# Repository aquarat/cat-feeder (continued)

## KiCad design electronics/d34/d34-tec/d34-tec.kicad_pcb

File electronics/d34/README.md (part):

# D34 hand-soldered controller (three vertical cards)

**Status: generated, ERC/DRC-checked design files. Not fabricated, not
soldered, not powered, no firmware.**

- Rationale, power budget, TVS analysis and open questions: [kb/d34-controller.md](../../kb/d34-controller.md).
- Decision: [D34](../../kb/decisions.md).

Bare 2-layer boards (1.6 mm FR-4, 1 oz), fabrication only. Every part is
through-hole or a plug-in module. Two upload packages per card:
`<card>-pcbtrain.zip` (PCB Train / Newbury Electronics, UK; recommended UK
fab) and `<card>-jlcpcb-gerbers.zip` (JLCPCB, much cheaper). Components:
RS Components UK except one Farnell line and two module retailers; the
sourced BOM, totals and fab comparison are in
[kb/d34-sourcing.md](../../kb/d34-sourcing.md).
3D envelopes for CAD: [`parts3d.json`](parts3d.json) (schema below).

All three cards are **81 × 47 mm**, sized to the CAD-checked bay (44 radial ×
85 tangential × 51 mm high). Each stands in a floor slot with its plane
tangential and components facing the axis. The top long edge takes a
printed clip. 3 mm long-edge bands are free of pads and courtyards.

| Card | Bay | Contents |
|---|---|---|
| [`d34-ctrl`](d34-ctrl/) | 45° | Socketed ESP32-DevKitC-32E, lid/leak/home/UI/DPS-UART headers, TEC watchdog (74HC123) and defrost latch (74HC573). Only 5 V and 3.3 V. |
| [`d34-pwr`](d34-pwr/) | 225° | 24 V brick entry, reverse FET, TVS, 7.5 A DPS fuse, 1.1 A PTC aux, TRACO 12 V 2 A / 5 V 1 A bucks, DPS5005 feed, StepStick (VMOT 12 V) + motor, one 1-Wire header per bus. |
| [`d34-tec`](d34-tec/) | 315° | K1 cut-off and K2 reversal relays (2N3904 low sides, K2 hold-up), thermostat loop, DPS output in, TEC out, three fan headers with IRLZ44N low sides and a 0.5 A polyfuse each. |

## Inter-card leads (keyed, same pin order both ends; checked by `test_d34.py`)

| Lead | Type | Pins |
|---|---|---|
| ctrl J1 ↔ pwr J9 | JST XH-11 | 1-2 +5 V, 3-4 GND, 5 +3V3, 6 STEP, 7 DIR, 8 EN, 9 TMC UART, 10 1-Wire A, 11 1-Wire B |
| ctrl J2 ↔ tec J9 | JST XH-12 | 1-2 GND, 3 K1_ON, 4 K2_ON, 5 THERMO_OK, 6 GND, 7-9 FAN1-3 PWM, 10-11 TACH1-2, 12 GND |
| pwr J3 → tec J1 | JST VH-3 | 1 +12 V, 2 GND, 3 +12 V |

## Card connectors

Pin 1 is the square pad or the silkscreen triangle.

| Card | Ref | Type | Pins |
|---|---|---|---|
| pwr | J1 | Mini-Fit Jr 2 | 1 +24 V in, 2 GND (brick) |
| pwr | J2 | Phoenix MSTB 2 | DPS5005 input: 1 IN+ (7.5 A fused), 2 IN− |
| pwr | J8 | JST VH-4 | Motor 2B 2A 1A 1B (17HS08-1004S: confirm coil pairs with a meter) |
| pwr | J4 / J6 | XH-3 | 1-Wire bus A (chamber air + food probes) / bus B (hot sink + room): GND, DQ, 3V3. The harness Y-splices each bus to its probes; more probes can join either bus. |
| tec | J2 | Mini-Fit Jr 6 | DPS5005 output: 1-3 OUT+, 4-6 OUT− (OUT− is **not** ground). The lead populates only pins 1 and 4 (one 18 AWG wire per pole, ≤ 5 A on a 9 A contact); the 6-way housing keeps it unpluggable into the 4-way TEC header. |
| tec | J3 | Mini-Fit Jr 4 | TEC 2S2P: 1 A, 2 B, 3 A, 4 B (one string per pair) |
| tec | J4 | JST VH-2 | Thermostat loop: 1 +12 V out, 2 return to K1 coil. Four RS PRO T24A060ASF2-15 NC (open 60 °C) in series. |
| tec | J5 | 4-pin fan | FAN1 (NF-A12x25): GND, +12 V via 0.5 A PTC, TACH, PWM (NPN open collector, **inverted**) |
| tec | J6 | 4-pin fan | FAN2 (blower): switched low side (IRLZ44N), +12 V via 0.5 A PTC, TACH, NC |
| tec | J7 | 4-pin fan | FAN3 spare: switched low side (IRLZ44N), +12 V via 0.5 A PTC, NC, NC (fan or external 12 V relay ≤ 0.4 A) |
| ctrl | J3 | XH-3 | Home sensor (DRV5023 hall, 3.3 V, open drain into the 10 k pull-up): GND, SIG, 3V3 |
| ctrl | J4 | XH-4 | SENSE: 1 GND, 2 LID (reed to GND, 10 k pull-up), 3 LEAK (basin-full pins, 47 k pull-up, 10 k series to ADC), 4 GND. Two cables, one housing. |
| ctrl | J6 | XH-5 | Panel: GND, 3V3, LED (330 Ω fitted), BUTTON (to GND), GND |
| ctrl | J11 | XH-4 | DPS5005 UART 3.3 V: GND, DPS-TX, DPS-RX, NC. DPS end: the 4-pin 1.25 mm (JST-GH type) comms socket; make the lead from the cable supplied with the DPS comms kit, meter GND and the idle-high TX first (see kb/d34-sourcing.md). |

**StepStick (pwr U4).** BIGTREETECH TMC2209 V1.3 is the intended driver
(pinout from BTT's V1.3 schematic, `datasheets/btt_tmc2209_v13_sch.pdf`).
- **VMOT is +12 V** from the TSR 2-24120N, not the 24 V brick, so the TVS
  clamp (30–33 V) can never reach the TMC2209 (32 V abs max).
- Pin 4 (PDN_UART) is wired to the ESP32 single-wire UART: TX via 1 k (ctrl
  R6), RX direct. BTT V1.3 has no series resistor on the module, so R6 is needed.
- Pins 5 and 6 are linked to each other only. BTT V1.3: pin 5 is not connected
  on the module, pin 6 is CLK with a 20 k pull-down (internal clock). A4988:
  RESET tied to SLEEP, which the Pololu carrier pulls up (Pololu's own advice).
- MS1/MS2 are open: the TMC2209's internal pull-downs give UART address 0.
- A Pololu A4988 also fits, but only at full step. Firmware must then hold
  IO17 low and keep IO16 as an input, so that MS3 = 0.

## ESP32 GPIO map

| GPIO | Use | GPIO | Use |
|---|---|---|---|
| IO0 | Button (also BOOT) | IO19 | EN (active low) |
| IO2 | Status LED (panel + on-board) | IO21 / IO22 | DPS RX / TX |
| IO4 / IO13 | 1-Wire A / B | IO23 | HOME |
| IO5 | FAN3 on/off | IO25 | DEFROST_REQ |
| IO12 | FAN1 PWM (10 k strap pull-down) | IO26 | DEFROST_FB |
| IO14 | FAN2 on/off (switched DC) | IO27 | LID |
| IO15 | DIR | IO32 | TEC_EN |
| IO16 / IO17 | TMC UART RX / TX | IO33 | WDT_KICK |
| IO18 | STEP | IO34 / IO35 | TACH1 / TACH2 |
| IO36 | THERMO_OK | IO39 | LEAK (ADC) |

## TEC firmware contract (hardware-enforced parts and firmware rules)

Revised 2026-10-26 after the simulation round ([kb/d34-simulation.md](../../kb/d34-simulation.md)).

1. **K1 closes only while all of these hold:**
   - TEC_EN (IO32) is high;
   - IO33 (WDT_KICK) shows rising edges at **≥ 10 Hz** (74HC123 timeout 470 k × 1 µF ≈ 0.47 s nominal,
     **0.32–0.65 s** over K = 0.69–1.36 at 3.3 V, C ±10 %, R ±1 %);
   - +12 V is present and every thermostat is closed (the K1 coil is fed through them).

   Reset, a crash, a stuck pin, an unplugged lead or a lost 12 V rail opens K1.
2. **Firmware rules the hardware cannot enforce:**
   - toggle WDT_KICK from the control loop in software, **never from a hardware PWM/LEDC/timer**
     (a hung CPU with a running PWM would keep K1 closed);
   - **never pulse TEC_EN as a keep-alive**: a TEC_EN rising edge while WDT_KICK is high retriggers the
     74HC123 through its CLR input;
   - read the blower tach (TACH2) only while FAN2 is fully on: FAN2/FAN3 are now **switched DC**
     (no 25 kHz PWM), and the tach is referenced to the switched ground. FAN1 keeps 25 kHz PWM (inverted).
3. **K2 (defrost polarity)** follows DEFROST_REQ only while the latch is transparent: K1 commanded off for
   longer than the 74HC123 half-2 delay (0.32–0.65 s). LE edges are now CMOS-fast. K2 also has a
   hold-up (C1 220 µF): after its drive drops it stays energised for up to ~0.25 s, so on any supply loss
   K1 (fast diode + 15 V zener release) always opens first. Defrost entry and exit:
   - DPS output off (Modbus);
   - TEC_EN low;
   - wait **≥ 0.8 s** (latch delay max 0.65 s);
   - set or clear DEFROST_REQ;
   - wait **≥ 400 ms** (K2 transfer; on exit K2 is held up to ~0.25 s by C1), then check DEFROST_FB;
   - re-arm (TEC_EN high + kicks), wait ≥ 50 ms for K1 to close;
   - only then DPS output on. **Keep the DPS output off until K1 is re-armed.**
4. **After any reset or brown-out** run the full contract from boot before re-arming K1: the 74HC573
   contents (K2 command) are undefined at power-up. Keep TEC_EN low and the DPS output off, drive
   DEFROST_REQ to the wanted state, wait ≥ 0.8 s (latch delay ≤ 0.65 s, so the latch has loaded it), wait
   ≥ 0.4 s, check DEFROST_FB, then re-arm and only then turn the DPS output on. Timings as in
   `sim/firmware_contract.json` (owned by the simulation agent).
5. **12 V undervoltage cut-off (hardware, tec card):** the thermostat loop that feeds K1's coil is switched
   by Q6 (BC327) under a TL431 comparator: K1 drops below ~9.4 V on +12 V and can re-close only above
   ~10.3 V. While it is tripped THERMO_OK reads low, the same as an open thermostat.
6. **THERMO_OK** (IO36) reads about 3.0 V (2.85–3.15 V) when the thermostat loop is closed; reading it with
   the ADC (threshold ~1.4 V) gives more margin than a digital read. IO36 is now fed through 47 k with a
   BAT42 clamp to GND (a thermostat opening drags the loop to about −15 V for a few ms).
7. **Reversed-brick ring snubber:** 2.2 Ω + 1 µF in series across the inlet socket's +24 V and 0 V pins
   (off-board, at the Kycon socket), keeping the reversed-plug ring at J1 within Q1's 55 V rating.

## Files (per card directory)

| File | Purpose |
|---|---|
| `<card>.kicad_pro/.kicad_sch/.kicad_pcb` | KiCad 9 project; local libs `d34.kicad_sym`, `../d34.pretty` |
| `<card>.kicad_dru` | Copy of [`../dfm/jlcpcb-2layer-recommended.kicad_dru`](../dfm/README.md) |
| `<card>-pcbtrain.zip`, `pcbtrain/` | Upload to PCB Train: RS-274X without X2, Excellon PTH/NPTH, README.txt |
| `<card>-jlcpcb-gerbers.zip`, `gerbers/` | Upload to JLCPCB (Gerber X2 + Excellon PTH/NPTH) |
| `<card>-bom.csv` | Card BOM with supplier, stock number, pack, datasheet and verification state; off-board mating parts |
| `erc.*`, `drc.*`, `validation.json` | Check results for exactly these files |
| `envelope.json` | Courtyards and body/mated heights for CAD |
| `views/` | `render-top/bottom.png`, `top/bottom/assembly.svg`, `schematic.pdf`, `board-only.step` |

Shared sources:
- `design.py`: connectivity, placement and hand-placed high-current copper.
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
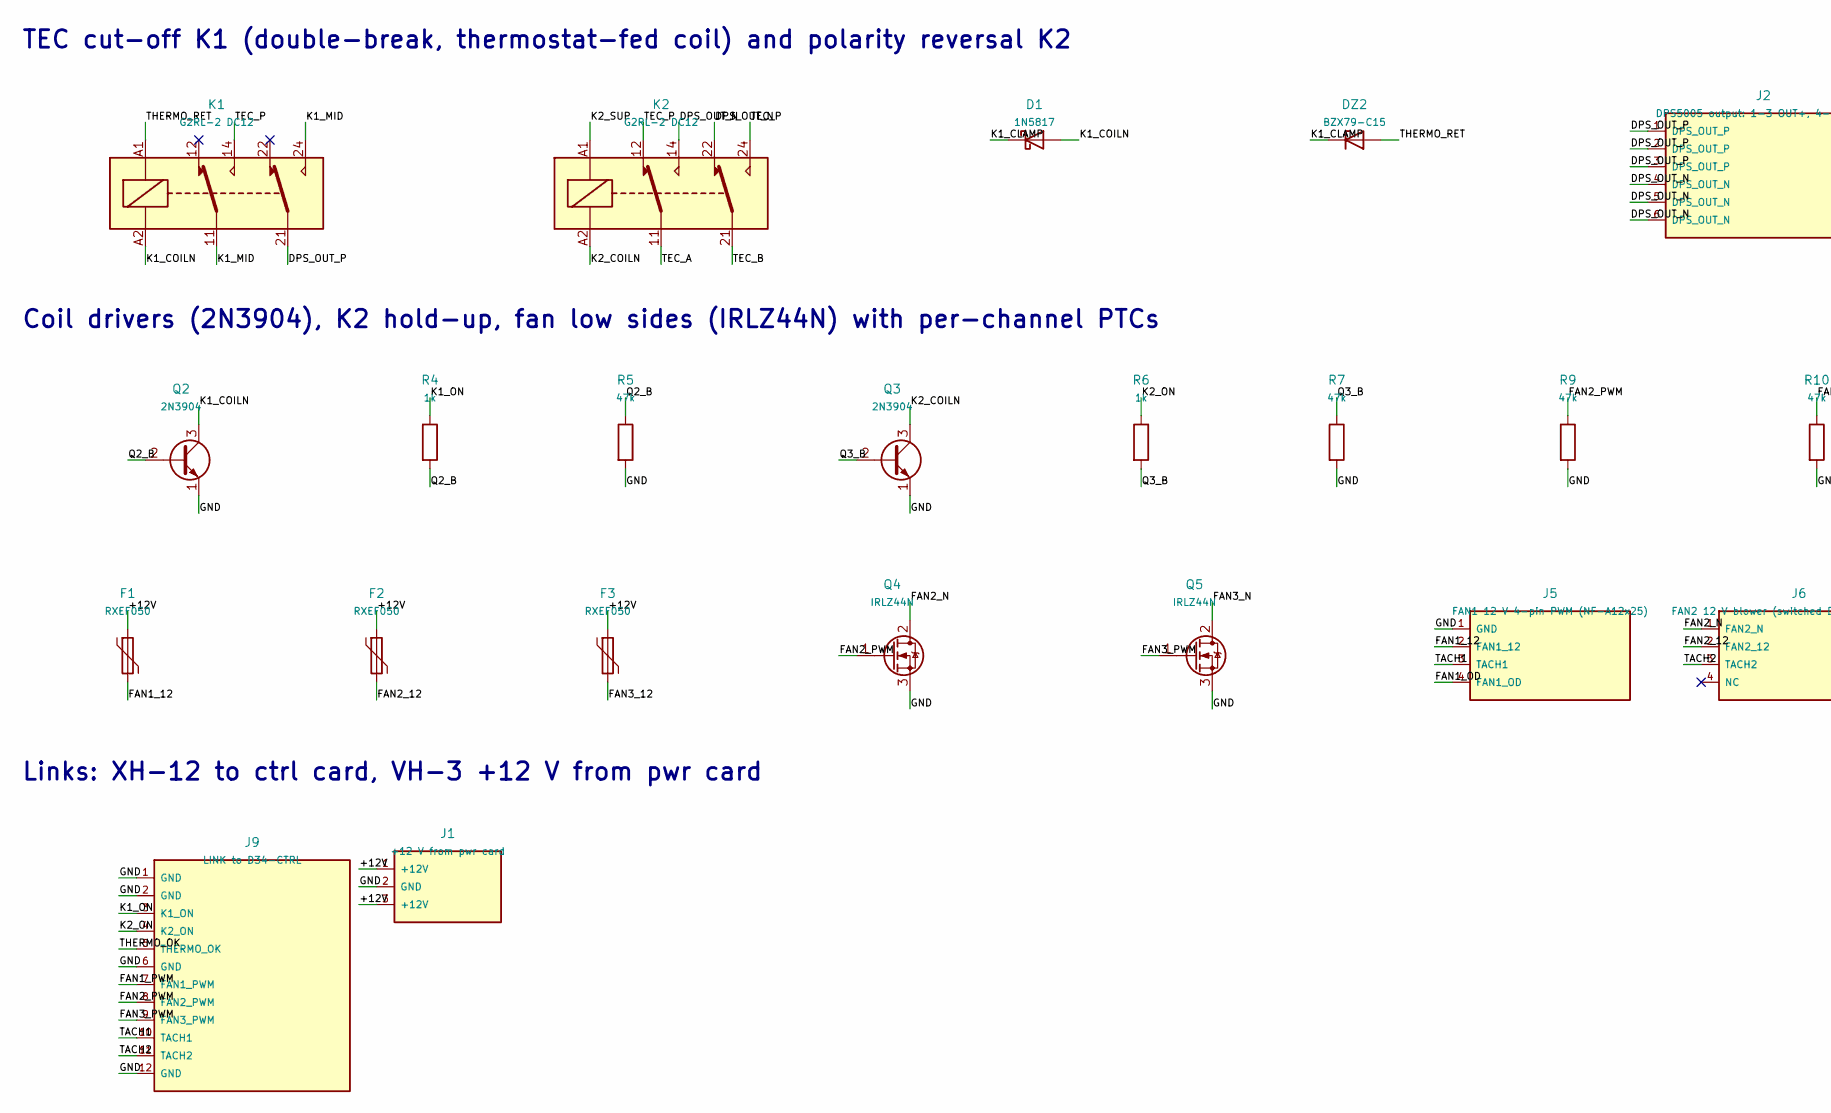
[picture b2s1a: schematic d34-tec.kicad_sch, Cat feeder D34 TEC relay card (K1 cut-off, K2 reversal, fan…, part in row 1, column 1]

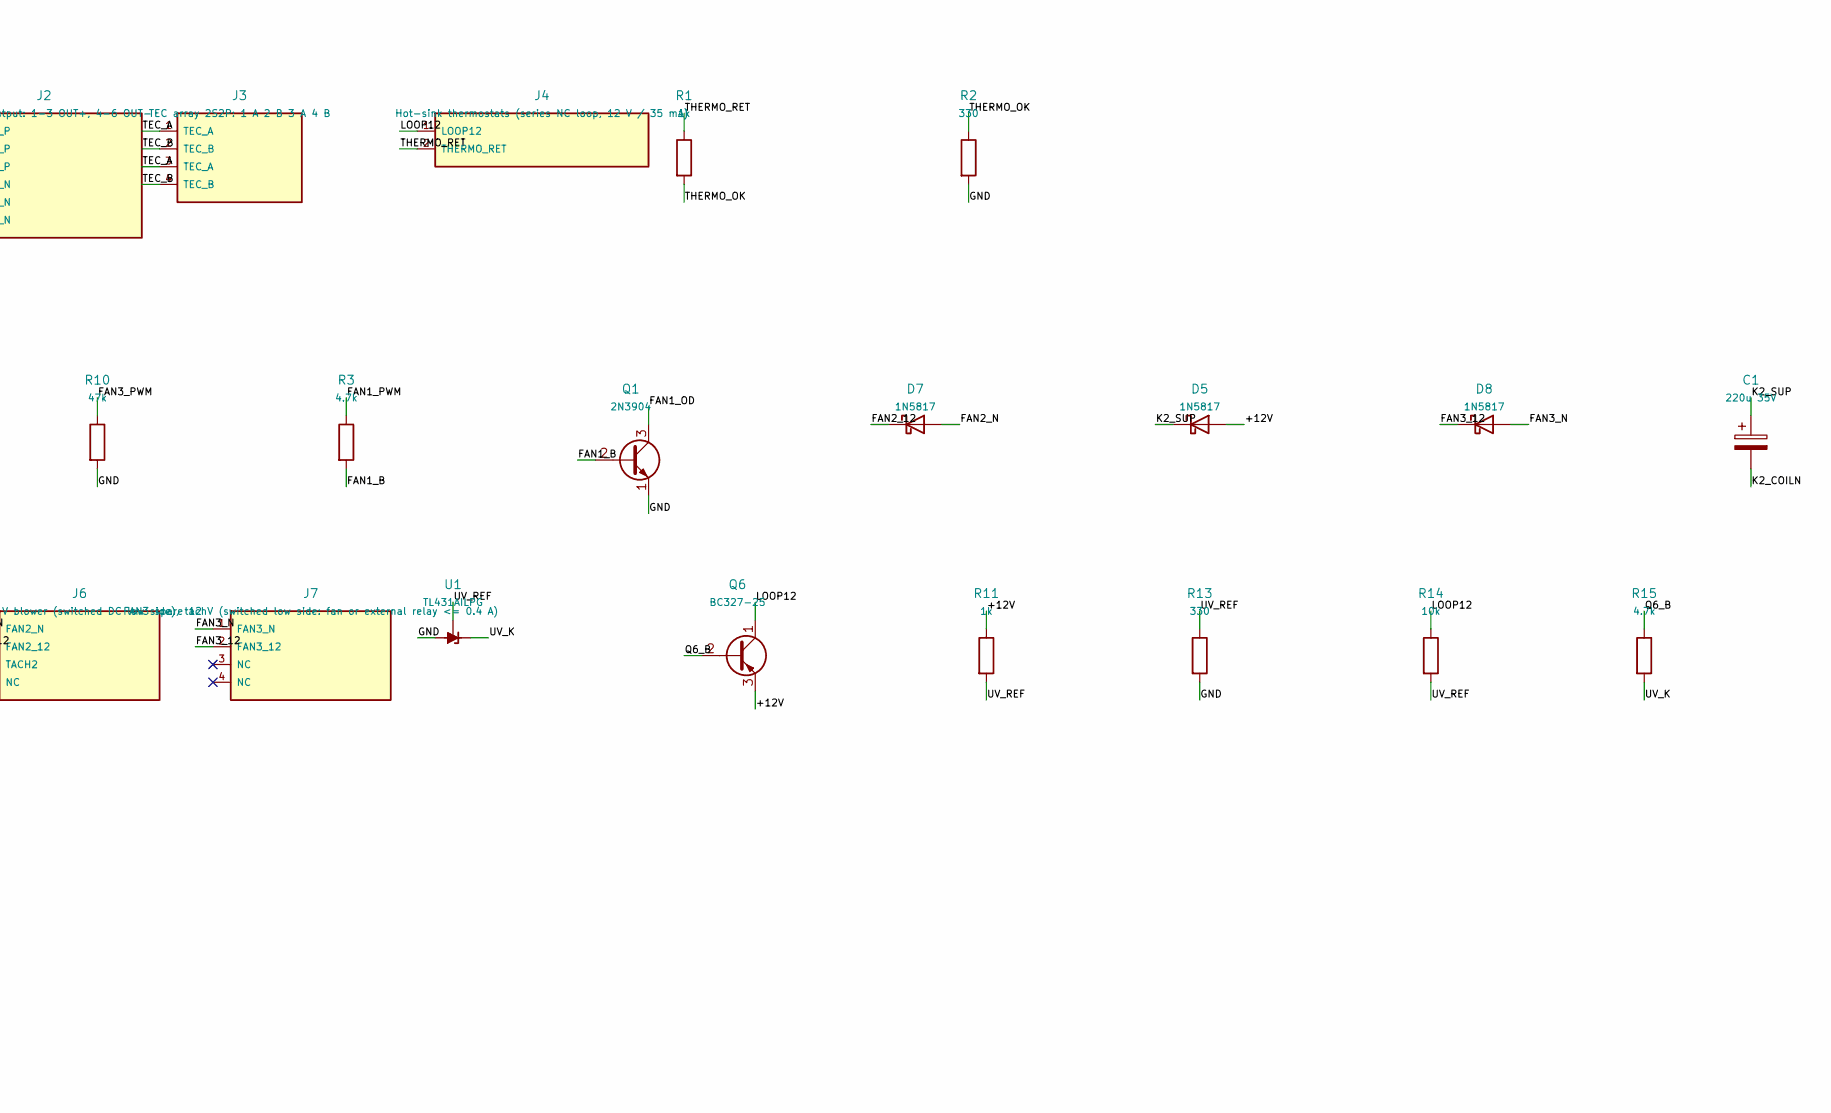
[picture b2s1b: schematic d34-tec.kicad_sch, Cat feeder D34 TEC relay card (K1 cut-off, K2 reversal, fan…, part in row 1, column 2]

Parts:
C1: 220u 35V; CP_Radial_D8.0mm_P3.50mm; MPN EEU-FR1V221
D1, D5, D7, D8: 1N5817; D_DO-41_SOD81_P2.54mm_Vertical_AnodeUp; MPN 1N5817RLG
DZ2: BZX79-C15; D_DO-35_SOD27_P2.54mm_Vertical_AnodeUp; MPN BZX79-C15,133
F1, F2, F3: RXEF050; PTC_Radial_L8.0mm_W3.2mm_P5.08mm; MPN RXEF050
J1: +12 V from pwr card; JST_VH_B3P-VH_1x03_P3.96mm_Vertical; MPN B3P-VH(LF)(SN)
J2: DPS5005 output: 1-3 OUT+, 4-6 OUT-; Molex_Mini-Fit_Jr_5566-06A_2x03_P4.20mm_Vertical; MPN 39-28-1063 (5566-06A)
J3: TEC array 2S2P: 1 A 2 B 3 A 4 B; Molex_Mini-Fit_Jr_5566-04A_2x02_P4.20mm_Vertical; MPN 39-28-1043 (5566-04A)
J4: Hot-sink thermostats (series NC loop, 12 V / 35 m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; JST_VH_B2P-VH_1x02_P3.96mm_Vertical; MPN B2P-VH(LF)(SN)
J5: FAN1 12 V 4-pin PWM (NF-A12x25); FanPinHeader_1x04_P2.54mm_Vertical; MPN 47053-1000
J6: FAN2 12 V blower (switched DC low side), tach; FanPinHeader_1x04_P2.54mm_Vertical; MPN 47053-1000
J7: FAN3 spare 12 V (switched low side: fan or extern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; FanPinHeader_1x04_P2.54mm_Vertical; MPN 47053-1000
J9: LINK to D34-CTRL; JST_XH_B12B-XH-A_1x12_P2.50mm_Vertical; MPN B12B-XH-A(LF)(SN)
K1, K2: G2RL-2 DC12; Relay_DPDT_Omron_G2RL-2; MPN G2RL-2 DC12
Q1, Q2, Q3: 2N3904; TO-92_Inline_Wide; MPN 2N3904BU
Q4, Q5: IRLZ44N; TO-220-3_Vertical; MPN IRLZ44NPBF
Q6: BC327-25; TO-92_Inline_Wide; MPN BC32725BU
R1, R4, R6, R11: 1k; R_Axial_DIN0204_L3.6mm_D1.6mm_P2.54mm_Vertical; MPN MF0204FTE52-1K
R2, R13: 330; R_Axial_DIN0204_L3.6mm_D1.6mm_P2.54mm_Vertical; MPN MF0204FTE52-330R
R3, R15: 4.7k; R_Axial_DIN0204_L3.6mm_D1.6mm_P2.54mm_Vertical; MPN MF0204FTE52-4K7
R5, R7, R9, R10: 47k; R_Axial_DIN0204_L3.6mm_D1.6mm_P2.54mm_Vertical; MPN MF0204FTE52-47K
R14: 10k; R_Axial_DIN0204_L3.6mm_D1.6mm_P2.54mm_Vertical; MPN MF0204FTE52-10K
U1: TL431AILPG; TO-92_Inline_Wide; MPN TL431AILPG

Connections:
/+12V: D5.2 (A), F1.1, F2.1, F3.1, J1.1 (+12V), J1.3 (+12V), Q6.3 (E), R11.1
/DPS_OUT_N: J2.4 (DPS_OUT_N), J2.5 (DPS_OUT_N), J2.6 (DPS_OUT_N), K2.14, K2.22
/DPS_OUT_P: J2.1 (DPS_OUT_P), J2.2 (DPS_OUT_P), J2.3 (DPS_OUT_P), K1.21
/FAN1_12: F1.2, J5.2 (FAN1_12)
/FAN1_B: Q1.2 (B), R3.2
/FAN1_OD: J5.4 (FAN1_OD), Q1.3 (C)
/FAN1_PWM: J9.7 (FAN1_PWM), R3.1
/FAN2_12: D7.1 (K), F2.2, J6.2 (FAN2_12)
/FAN2_N: D7.2 (A), J6.1 (FAN2_N), Q4.2 (D)
/FAN2_PWM: J9.8 (FAN2_PWM), Q4.1 (G), R9.1
/FAN3_12: D8.1 (K), F3.2, J7.2 (FAN3_12)
/FAN3_N: D8.2 (A), J7.1 (FAN3_N), Q5.2 (D)
/FAN3_PWM: J9.9 (FAN3_PWM), Q5.1 (G), R10.1
/GND: J1.2 (GND), J5.1 (GND), J9.1 (GND), J9.2 (GND), J9.6 (GND), J9.12 (GND), Q1.1 (E), Q2.1 (E), Q3.1 (E), Q4.3 (S), Q5.3 (S), R2.2, R5.2, R7.2, R9.2, R10.2, R13.2, U1.2 (A)
/K1_CLAMP: D1.1 (K), DZ2.1 (K)
/K1_COILN: D1.2 (A), K1.A2, Q2.3 (C)
/K1_MID: K1.11, K1.24
/K1_ON: J9.3 (K1_ON), R4.1
/K2_COILN: C1.2, K2.A2, Q3.3 (C)
/K2_ON: J9.4 (K2_ON), R6.1
/K2_SUP: C1.1, D5.1 (K), K2.A1
/LOOP12: J4.1 (LOOP12), Q6.1 (C), R14.1
/Q2_B: Q2.2 (B), R4.2, R5.1
/Q3_B: Q3.2 (B), R6.2, R7.1
/Q6_B: Q6.2 (B), R15.1
/TACH1: J5.3 (TACH1), J9.10 (TACH1)
/TACH2: J6.3 (TACH2), J9.11 (TACH2)
/TEC_A: J3.1 (TEC_A), J3.3 (TEC_A), K2.11
/TEC_B: J3.2 (TEC_B), J3.4 (TEC_B), K2.21
/TEC_P: K1.14, K2.12, K2.24
/THERMO_OK: J9.5 (THERMO_OK), R1.2, R2.1
/THERMO_RET: DZ2.2 (A), J4.2 (THERMO_RET), K1.A1, R1.1
/UV_K: R15.2, U1.3 (K)
/UV_REF: R11.2, R13.1, R14.2, U1.1 (REF)

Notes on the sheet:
TEC cut-off K1 (double-break, thermostat-fed coil) and polarity reversal K2
Coil drivers (2N3904), K2 hold-up, fan low sides (IRLZ44N) with per-channel PTCs
Links: XH-12 to ctrl card, VH-3 +12 V from pwr card

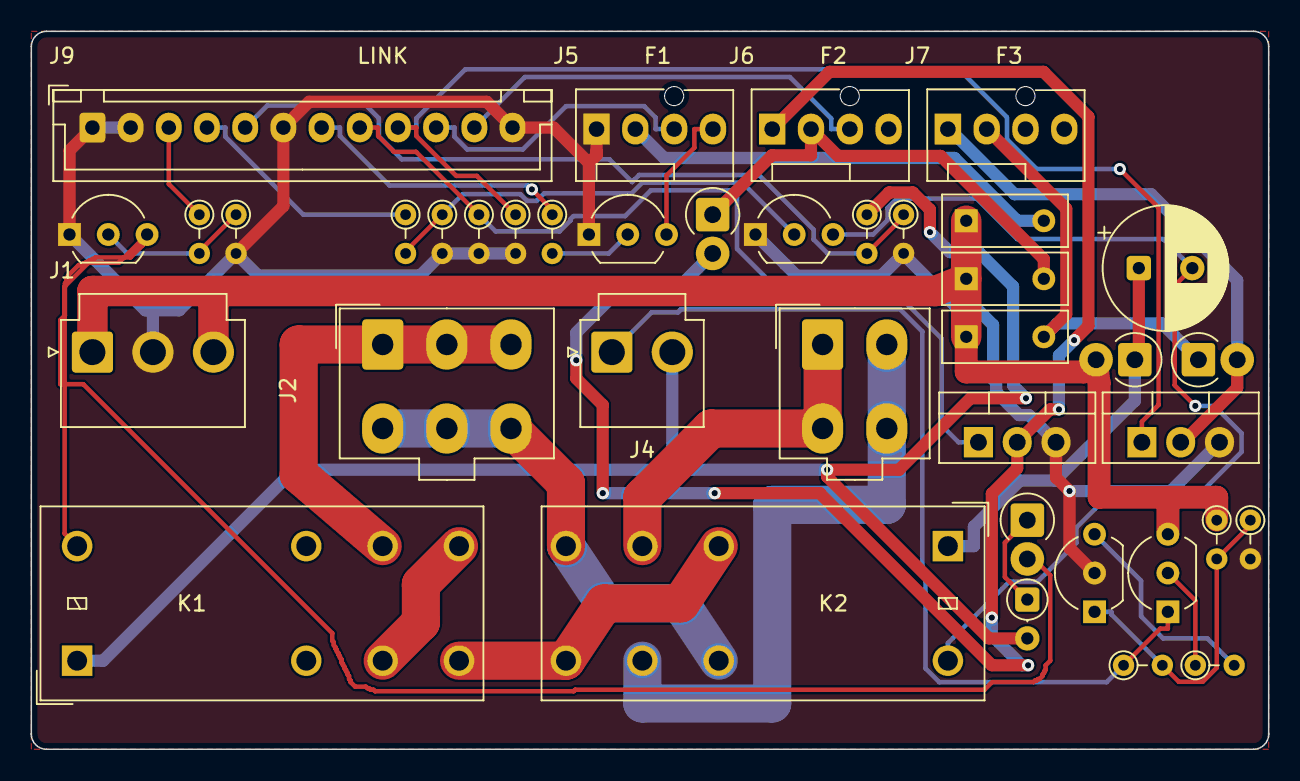
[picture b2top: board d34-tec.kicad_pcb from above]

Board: 2 copper layers, 81.0 x 47.0 mm, 39 parts (0 on the bottom side), 34 nets.

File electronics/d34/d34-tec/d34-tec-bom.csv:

Board,References,Qty,Value,Description,Manufacturer,MPN,KiCad footprint,Supplier,Stock no,Pack,Datasheet,Checked
d34-tec,K1 K2,2,,"DPDT relay 8 A, 12 V coil",Omron,G2RL-2 DC12,Relay_THT:Relay_DPDT_Omron_G2RL-2,RS,365-0585,1,omron_g2rl.pdf,"verified: 29 x 12.7 x 15.7 max, 1.3 mm holes on the KiCad grid, 33.3 mA / 360 ohm, 8 A 30 VDC (p2, p6); RS title says ""Aratas"" but listing is Omron, check marking on arrival"
d34-tec,D1 D7 D5 D8,4,,"Schottky 20 V 1 A, DO-41, mounted vertical",onsemi,1N5817RLG,Diode_THT:D_DO-41_SOD81_P2.54mm_Vertical_AnodeUp,RS,625-4972,5,1n5817-19.pdf,"verified: VF max 0.32 V @ 0.1 A, 0.45 V @ 1 A; 20 V; DO-41 (onsemi p2)"
d34-tec,DZ2,1,,"Zener 15 V 0.5 W, DO-35, mounted vertical (K1 fast-release clamp)",Nexperia,"BZX79-C15,133",Diode_THT:D_DO-35_SOD27_P2.54mm_Vertical_AnodeUp,RS,136-4852,100,bzx79.pdf,"verified: Vz 13.8-15.6 V @ 5 mA; SOD27 4.25 x 1.85 mm (p5, p9)"
d34-tec,J2,1,,6-pin Mini-Fit Jr vertical header,Molex,39-28-1063 (5566-06A),Connector_Molex:Molex_Mini-Fit_Jr_5566-06A_2x03_P4.20mm_Vertical,RS,484-1906,5,molex_5566_header.pdf,verified: SD-5566-002 (as 2-pin)
d34-tec,J3,1,,4-pin Mini-Fit Jr vertical header,Molex,39-28-1043 (5566-04A),Connector_Molex:Molex_Mini-Fit_Jr_5566-04A_2x02_P4.20mm_Vertical,RS,484-1899,5,molex_5566_header.pdf,verified: SD-5566-002 (as 2-pin)
d34-tec,J4,1,,2-pin JST VH header,JST,B2P-VH(LF)(SN),Connector_JST:JST_VH_B2P-VH_1x02_P3.96mm_Vertical,RS,820-1147,5,jst_vh.pdf,"verified: eVH pitch 3.96, hole 1.65-1.75, h 10.9, mated 16.5"
d34-tec,R1 R4 R6 R11,4,,"Resistor, metal film MF0204, 0.4 W, 1 %, axial, mounted vertical (2.54 mm)",Yageo,MF0204FTE52-1K,Resistor_THT:R_Axial_DIN0204_L3.6mm_D1.6mm_P2.54mm_Vertical,RS,199-7806,100,yageo_mf0.pdf,"verified: body 3.4+-0.3 x 1.9+-0.2 mm, lead 0.45 mm, M-forming P 6.0 mm (Yageo MF0 spec p3, p9)"
d34-tec,R2 R13,2,,"Resistor, metal film MF0204, 0.4 W, 1 %, axial, mounted vertical (2.54 mm)",Yageo,MF0204FTE52-330R,Resistor_THT:R_Axial_DIN0204_L3.6mm_D1.6mm_P2.54mm_Vertical,RS,199-7821,100,yageo_mf0.pdf,"verified: body 3.4+-0.3 x 1.9+-0.2 mm, lead 0.45 mm, M-forming P 6.0 mm (Yageo MF0 spec p3, p9)"
d34-tec,Q2 Q3 Q1,3,,"NPN 40 V 200 mA, TO-92",onsemi,2N3904BU,Package_TO_SOT_THT:TO-92_Inline_Wide,RS,843-1575,50,2n3904.pdf,"verified: E-B-C facing the flat, straight leads 1.15-1.39 mm, body 5.2 x 4.2 x 5.33 (p1, p7); h incl. ~2.5 mm standoff"
d34-tec,R5 R7 R9 R10,4,,"Resistor, metal film MF0204, 0.4 W, 1 %, axial, mounted vertical (2.54 mm)",Yageo,MF0204FTE52-47K,Resistor_THT:R_Axial_DIN0204_L3.6mm_D1.6mm_P2.54mm_Vertical,RS,199-7828,100,yageo_mf0.pdf,"verified: body 3.4+-0.3 x 1.9+-0.2 mm, lead 0.45 mm, M-forming P 6.0 mm (Yageo MF0 spec p3, p9)"
d34-tec,R3 R15,2,,"Resistor, metal film MF0204, 0.4 W, 1 %, axial, mounted vertical (2.54 mm)",Yageo,MF0204FTE52-4K7,Resistor_THT:R_Axial_DIN0204_L3.6mm_D1.6mm_P2.54mm_Vertical,RS,199-7830,100,yageo_mf0.pdf,"verified: body 3.4+-0.3 x 1.9+-0.2 mm, lead 0.45 mm, M-forming P 6.0 mm (Yageo MF0 spec p3, p9)"
d34-tec,C1,1,,"220 uF 35 V low-ESR electrolytic, 8 x 11.5 mm (K2 hold-up)",Panasonic,EEU-FR1V221,Capacitor_THT:CP_Radial_D8.0mm_P3.50mm,RS,766-0078,10,panasonic_fr.pdf,Panasonic FR (same 8 x 11.5 mm case/3.5 mm pitch as EEU-FR1H101 per FR p1/p6): 220 uF 35 V
d34-tec,F1 F2 F3,3,,Resettable PTC 0.5 A hold (per fan channel),Littelfuse,RXEF050,d34:PTC_Radial_L8.0mm_W3.2mm_P5.08mm,RS,517-6635,10,littelfuse_rxef.pdf,"verified: 0.50 A hold / 1.00 A trip, 72 V, 7.9 wide x 3.0 thick x 13.7 high max, spacing 4.3-5.8, lead 0.51 (RXEF p2, p4, p6)"
d34-tec,Q4 Q5,2,,"Logic-level N-MOSFET, TO-220 (fan low side; survives a PTC-limited short)",Infineon,IRLZ44NPBF,Package_TO_SOT_THT:TO-220-3_Vertical,Farnell,8651418,1,irlz44n.pdf,"Infineon datasheet saved: logic-level N-FET 55 V 47 A, VGS(th) 1.0-2.0 V, RDS(on) 35 mOhm at 4 V, TO-220 G-D-S (PDF text not machine-readable: values read from the Infineon table, cross-checked with Farnell listing)"
d34-tec,J5 J6 J7,3,,4-pin PC fan header,Molex,47053-1000,Connector:FanPinHeader_1x04_P2.54mm_Vertical,RS,144-8185,10,molex_47053.pdf,"verified: SD-47053-001 pitch 2.54, holes 1.02, peg hole 1.25 (footprint corrected), pins 10.0 high"
d34-tec,U1,1,,"Shunt reference 2.495 V, TO-92 (12 V undervoltage cut-off for K1)",onsemi,TL431AILPG,Package_TO_SOT_THT:TO-92_Inline_Wide,RS,774-3697,10,tl431.pdf,"verified: TO-92 pin 1 Reference, 2 Anode, 3 Cathode (onsemi TL431/D, case 29); Vref 2.495 V +-1 % (A grade)"
d34-tec,Q6,1,,"PNP 45 V 0.8 A, TO-92 (thermostat-loop supply switch)",onsemi,BC32725BU,Package_TO_SOT_THT:TO-92_Inline_Wide,RS,765-315,100,bc327.pdf,"onsemi BC327: PNP -45 V -800 mA; TO-92 pin 1 C, 2 B, 3 E (case 29 style 17, as KiCad BC327); bulk leads splayed to 2.54 mm"
d34-tec,R14,1,,"Resistor, metal film MF0204, 0.4 W, 1 %, axial, mounted vertical (2.54 mm)",Yageo,MF0204FTE52-10K,Resistor_THT:R_Axial_DIN0204_L3.6mm_D1.6mm_P2.54mm_Vertical,RS,199-7794,100,yageo_mf0.pdf,"verified: body 3.4+-0.3 x 1.9+-0.2 mm, lead 0.45 mm, M-forming P 6.0 mm (Yageo MF0 spec p3, p9)"
d34-tec,J9,1,,12-pin JST XH shrouded header,JST,B12B-XH-A(LF)(SN),Connector_JST:JST_XH_B12B-XH-A_1x12_P2.50mm_Vertical,RS,820-1539,10,jst_xh.pdf,"verified: eXH pitch 2.5, length 2.5(n-1)+4.9, h 7.0, hole 0.9-1.0, mated 9.8"
d34-tec,J1,1,,3-pin JST VH header,JST,B3P-VH(LF)(SN),Connector_JST:JST_VH_B3P-VH_1x03_P3.96mm_Vertical,RS,820-1150,5,jst_vh.pdf,"verified: eVH pitch 3.96, hole 1.65-1.75, h 10.9, mated 16.5"
d34-tec,(off-board),1,,"Reverse-brick ring snubber, resistor: 2.2 ohm MRS25, in series with a 1 uF 50 V MLCC (Murata RDER71H105K2P1H03B, from the C1u pack) across the Kycon inlet socket (+24 V pins 1/4 to 0 V pins 2/3), heat-shrunk",Vishay,MRS25000C2208FCT00,,RS,683-3487,25,mrs25.pdf,Vishay MRS25 2R2 0.6 W (off-board: no bend-pitch limit)
d34-tec,(off-board),1,,Mini-Fit Jr receptacle housing 4-way (TEC lead),Molex,39-01-2040,,RS,484-1754,5,molex_5557_housing.pdf,
d34-tec,(off-board),1,,Mini-Fit Jr receptacle housing 6-way (DPS5005 output lead),Molex,39-01-2060,,RS,484-1760,5,molex_5557_housing.pdf,
d34-tec,(off-board),6,,"Molex Mini-Fit Jr pre-crimped lead, 225 mm 18 AWG, 39-00-0039-type socket one end, other end bare (W32 brick inlet 2 + W06 TEC feed 4); not stocked by RS",Molex,215341-1113,,Farnell,3559249,1,molex_39000039.pdf,retailer data (Farnell listing)
d34-tec,(off-board),2,,"Molex Mini-Fit Jr pre-crimped lead, 450 mm 18 AWG, one end bare (W05 DPS output, 290 mm needed: pins 1 and 4). Farnell showed 0 stock on 2026-10-26: if still out, use a 225 mm lead + soldered extension (heat-shrink RS 398-212)",Molex,215341-1115,,Farnell,3559251,1,molex_39000039.pdf,retailer data (Farnell listing)
d34-tec,(off-board),1,,JST VH housing 2-way (thermostat loop lead),JST,VHR-2N,,RS,820-1172,5,jst_vh.pdf,
d34-tec,(off-board),9,,"JST VH pre-crimped lead, 300 mm 20 AWG, SVH contact both ends (3 for the 12 V link W03; motor W13 (4) and thermostat W23, W27 (2) cut near one end)",JST,01SVHSVH-20L-300,,RS,820-1135,5,jst_vh.pdf,retailer data (RS listing)
d34-tec,(off-board),4,,"Bimetal thermostat NC, opens 60 C / closes 45 C, 16 A, 250 V AC/DC (one per hot sink, wired in series)",RS PRO,T24A060ASF2-15,,RS,222-8227,1,,"RS product page only (no datasheet published): NC, opens 60 C / closes 45 C, 16 A 250 V AC/DC, 6.3 mm tabs assumed; switches only 12 V / 35 mA here. Size and tab width UNVERIFIED until parts arrive"

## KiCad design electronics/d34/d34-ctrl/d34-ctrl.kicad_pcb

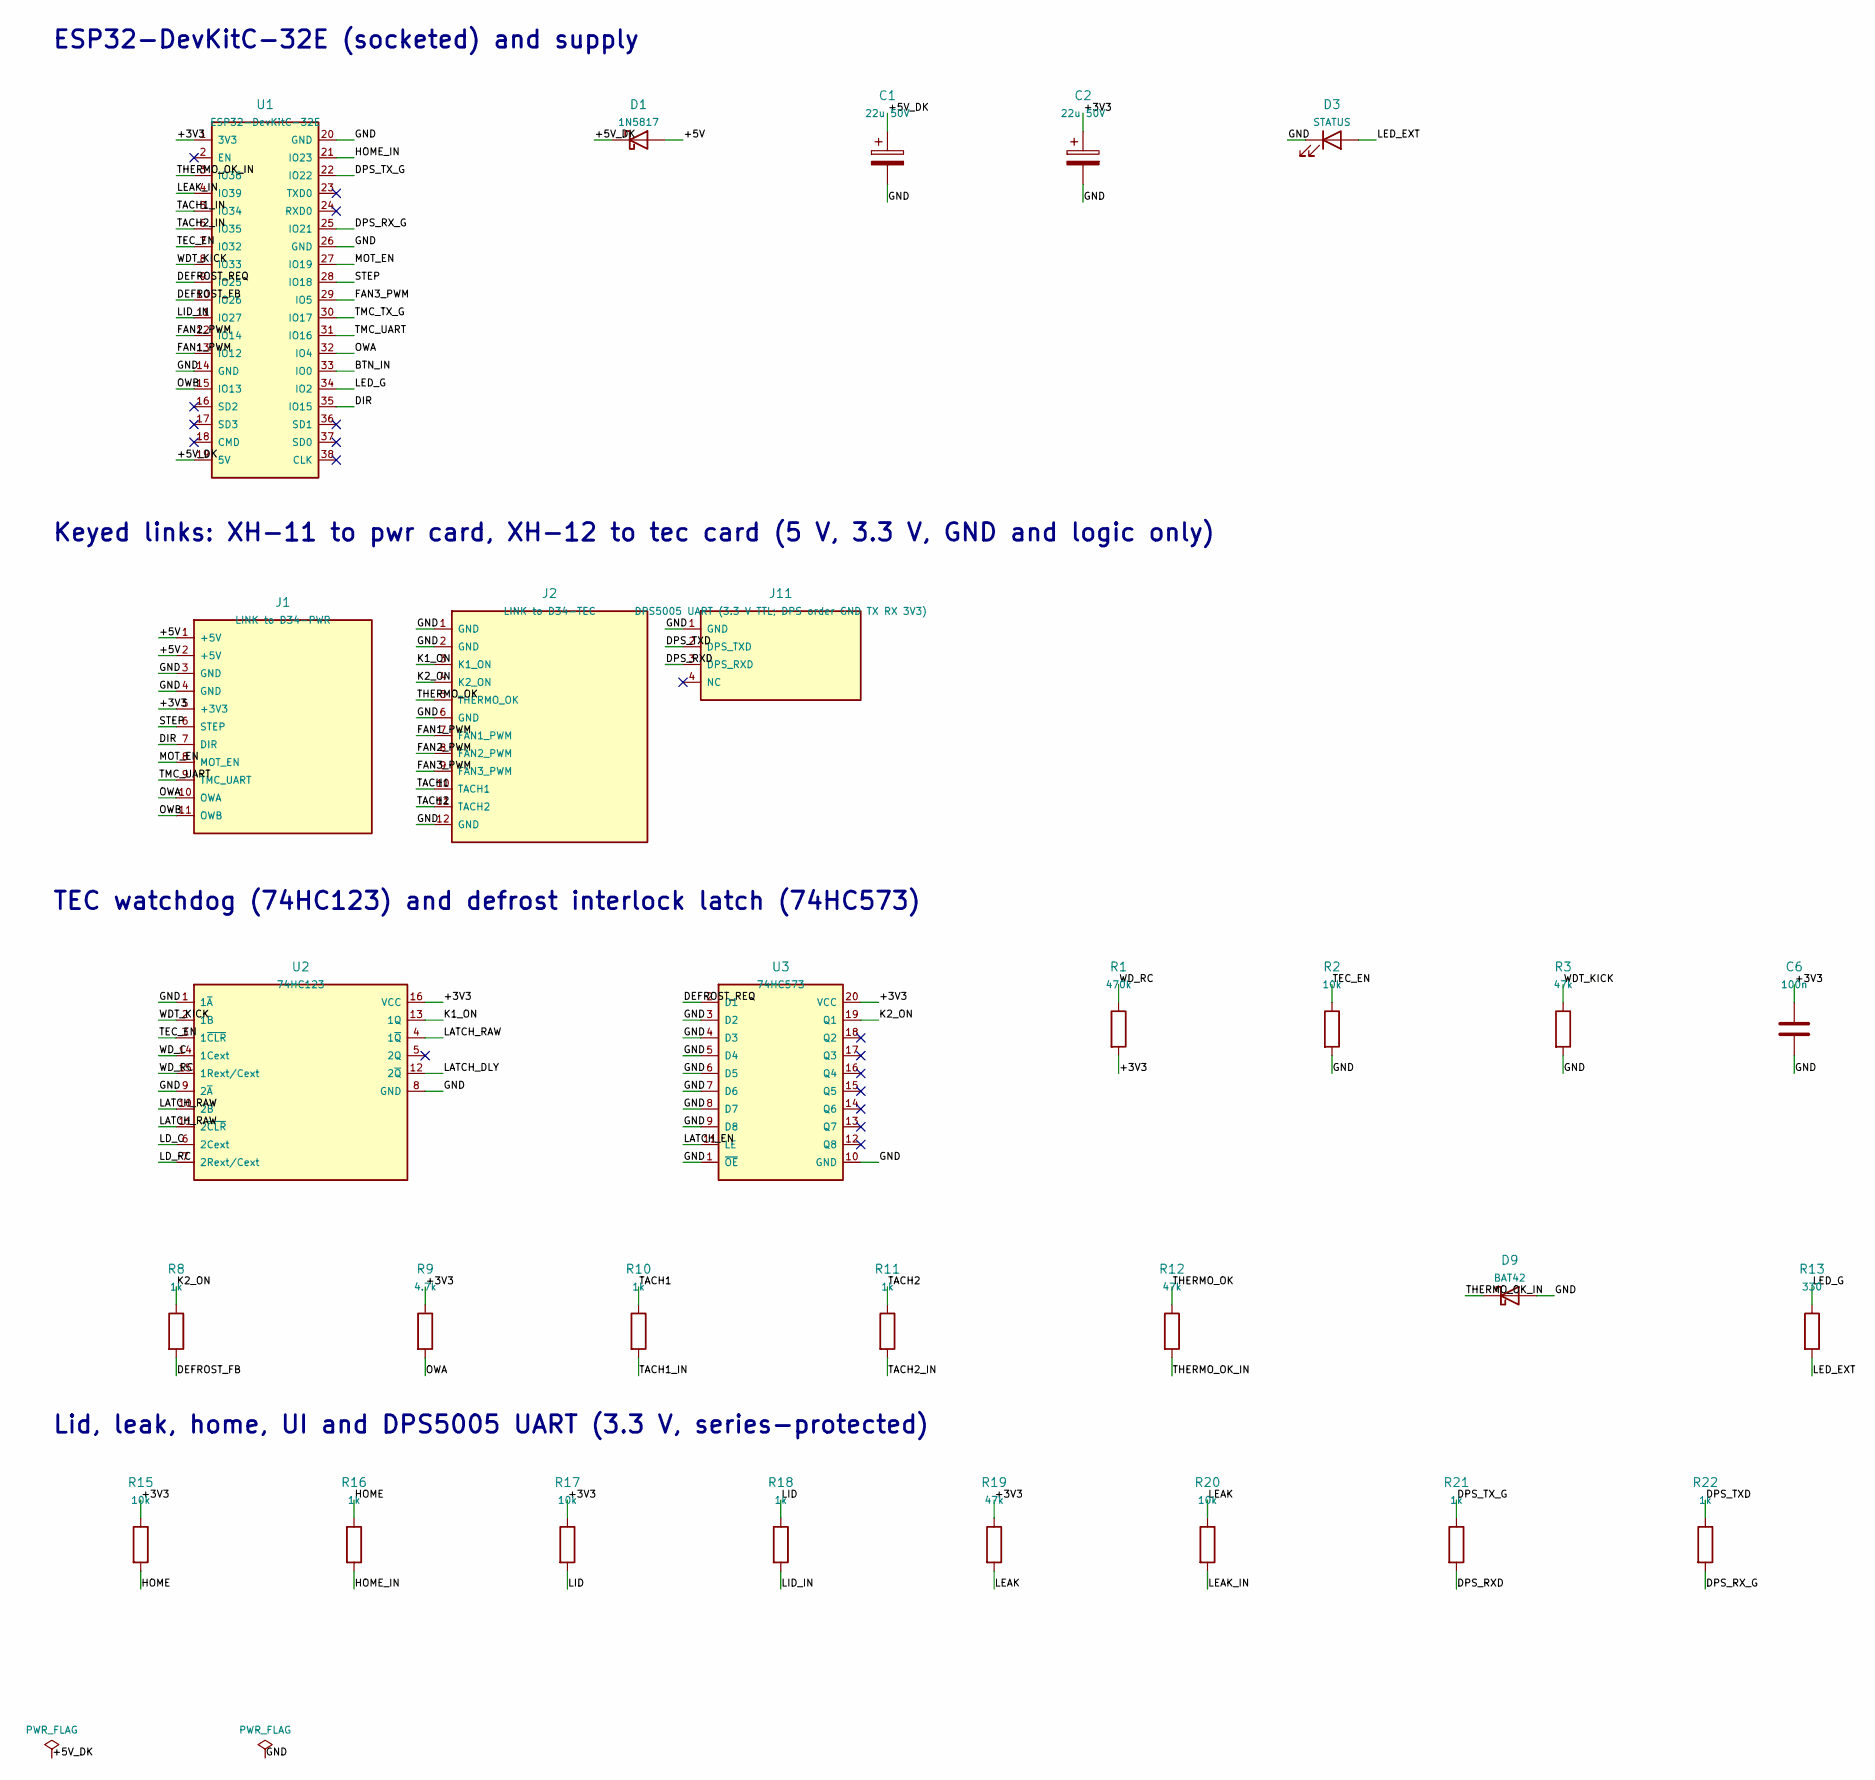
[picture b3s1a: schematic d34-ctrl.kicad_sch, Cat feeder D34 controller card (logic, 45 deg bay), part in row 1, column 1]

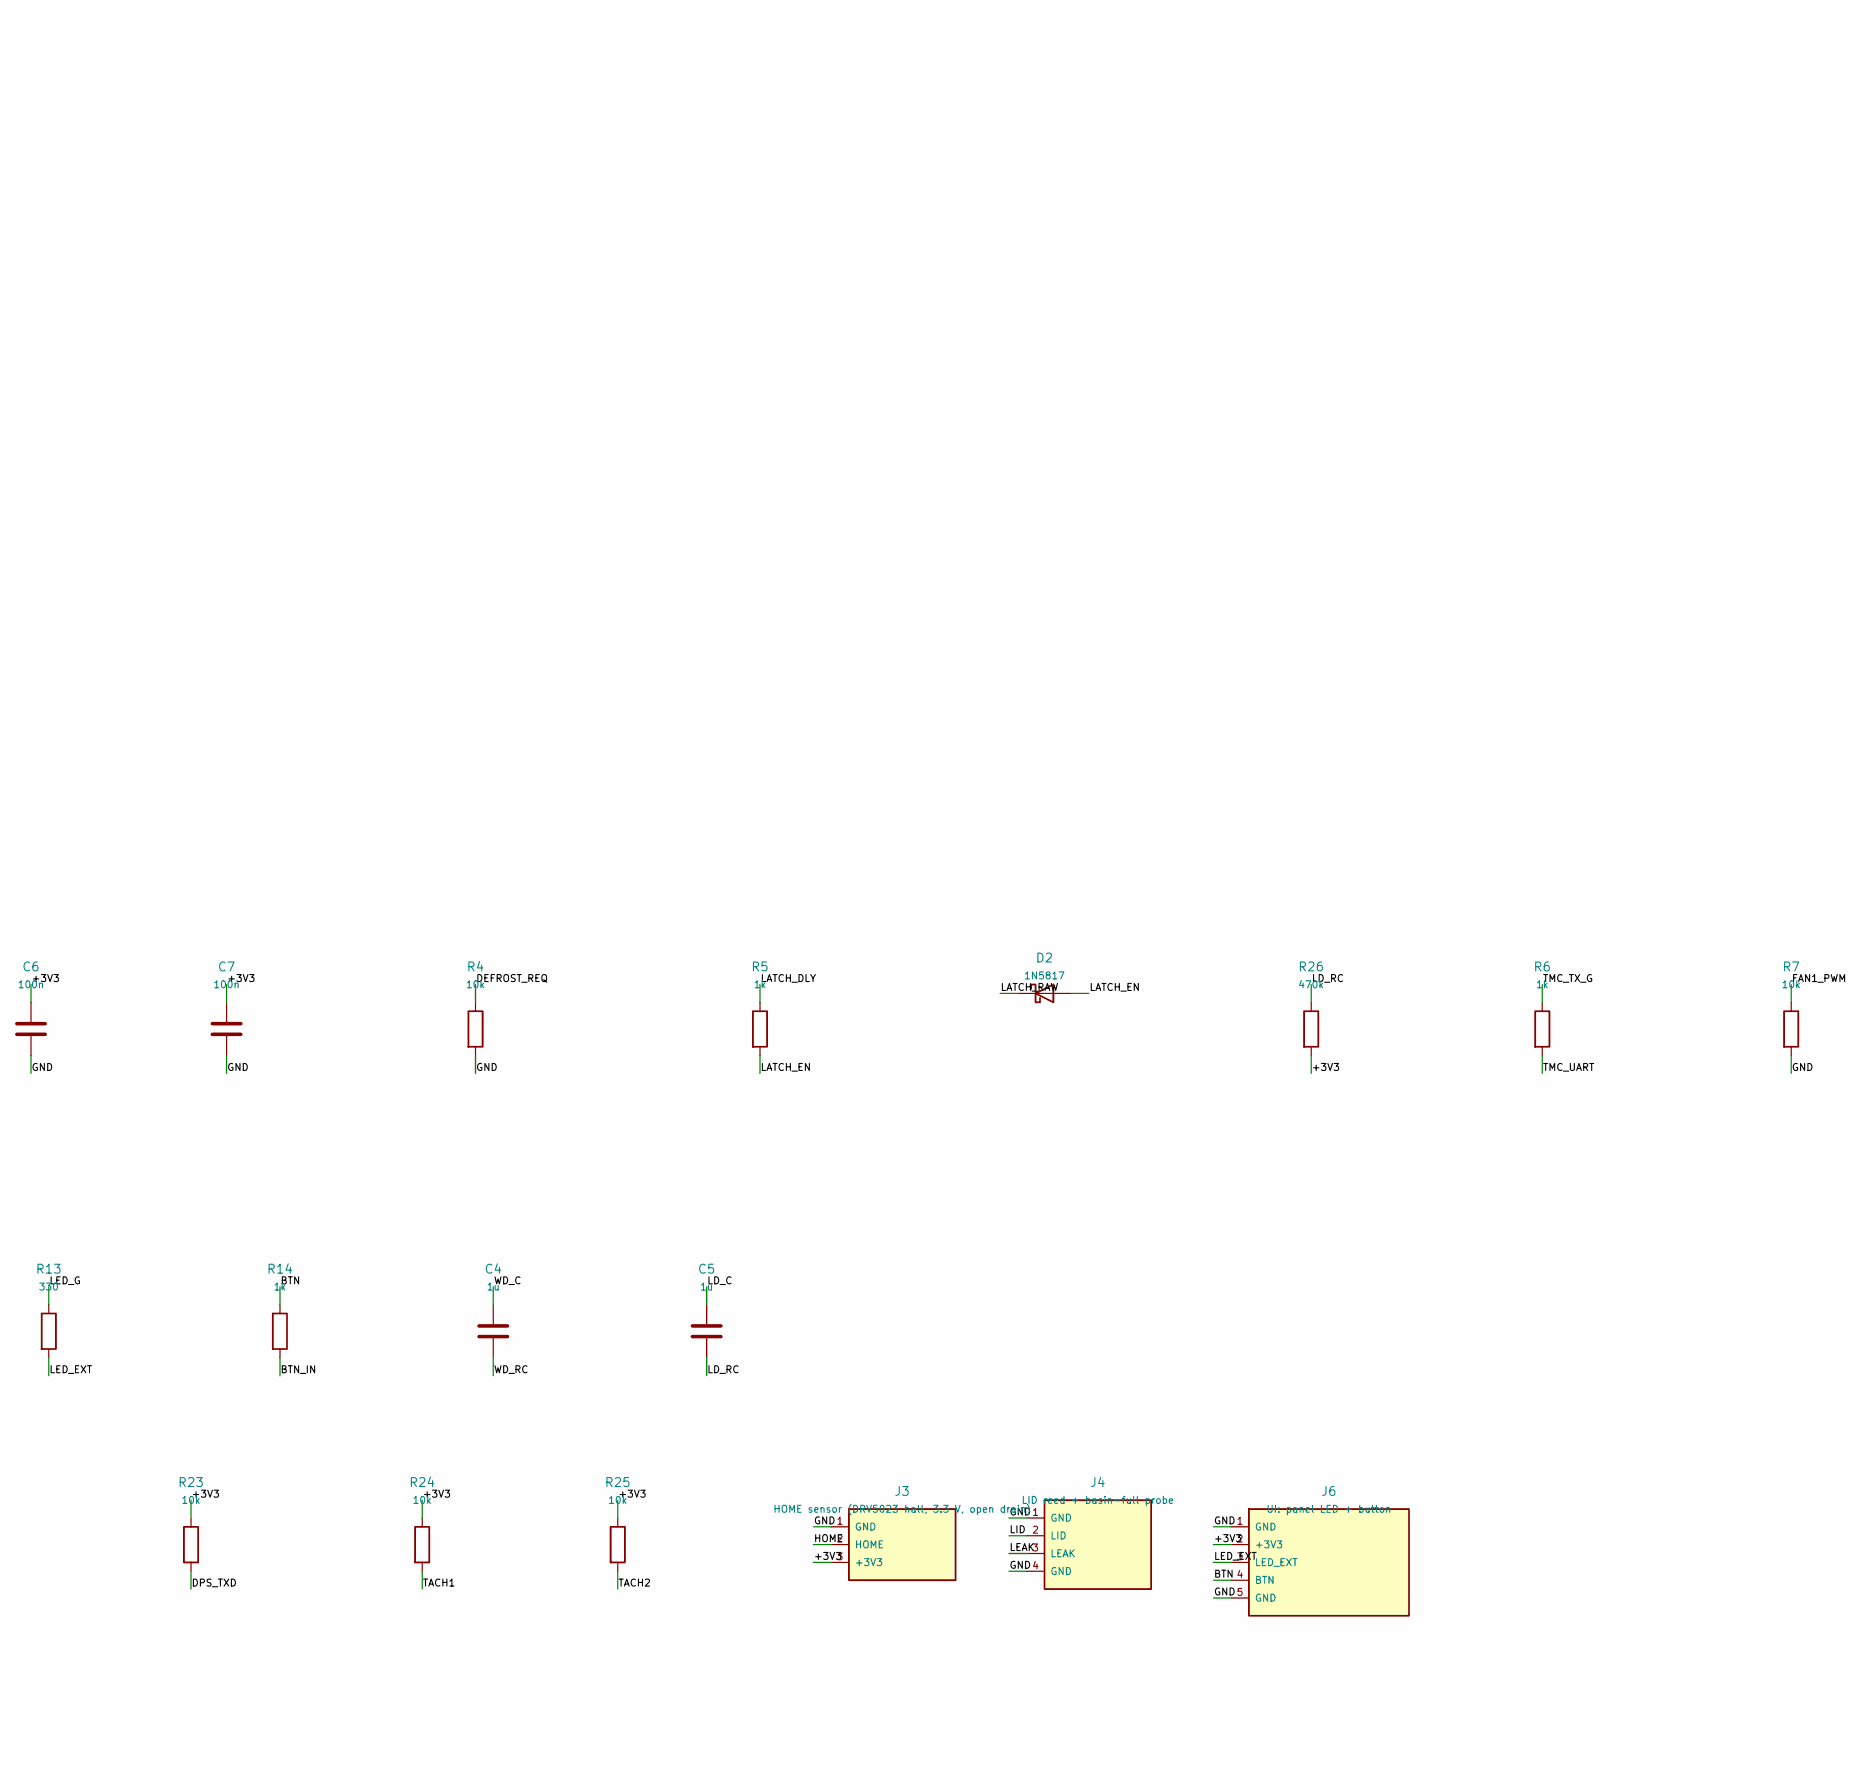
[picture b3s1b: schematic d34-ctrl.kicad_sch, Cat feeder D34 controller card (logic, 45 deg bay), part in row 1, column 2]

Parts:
C1, C2: 22u 50V; CP_Radial_D5.0mm_P2.00mm; MPN 50YXF22M5X11
C4, C5: 1u; C_Rect_L5.5mm_W3.2mm_P2.50mm; MPN RDER71H105K2P1H03B
C6, C7: 100n; C_Rect_L4.0mm_W2.5mm_P2.50mm; MPN RDER71H104K0P1H03B
D1: 1N5817; D_DO-41_SOD81_P10.16mm_Horizontal; MPN 1N5817RLG
D2: 1N5817; D_DO-41_SOD81_P2.54mm_Vertical_AnodeUp; MPN 1N5817RLG
D3: STATUS; LED_D3.0mm; MPN HLMP-1503
D9: BAT42; D_DO-35_SOD27_P2.54mm_Vertical_AnodeUp; MPN BAT42
J1: LINK to D34-PWR; JST_XH_B11B-XH-A_1x11_P2.50mm_Vertical; MPN B11B-XH-A(LF)(SN)
J2: LINK to D34-TEC; JST_XH_B12B-XH-A_1x12_P2.50mm_Vertical; MPN B12B-XH-A(LF)(SN)
J3: HOME sensor (DRV5023 hall, 3.3 V, open drain); JST_XH_B3B-XH-A_1x03_P2.50mm_Vertical; MPN B3B-XH-A(LF)(SN)
J4: LID reed + basin-full probe; JST_XH_B4B-XH-A_1x04_P2.50mm_Vertical; MPN B4B-XH-A(LF)(SN)
J6: UI: panel LED + button; JST_XH_B5B-XH-A_1x05_P2.50mm_Vertical; MPN B5B-XH-A(LF)(SN)
J11: DPS5005 UART (3.3 V TTL; DPS order GND TX RX 3V3); JST_XH_B4B-XH-A_1x04_P2.50mm_Vertical; MPN B4B-XH-A(LF)(SN)
R1: 470k; R_Axial_DIN0204_L3.6mm_D1.6mm_P7.62mm_Horizontal; MPN MBA02040C4703FRP00
R2, R4, R7, R15, R17, R20, R23, R24, R25: 10k; R_Axial_DIN0204_L3.6mm_D1.6mm_P7.62mm_Horizontal; MPN MF0204FTE52-10K
R3, R12, R19: 47k; R_Axial_DIN0204_L3.6mm_D1.6mm_P7.62mm_Horizontal; MPN MF0204FTE52-47K
R5, R6, R8, R10, R11, R14, R16, R18, R21, R22: 1k; R_Axial_DIN0204_L3.6mm_D1.6mm_P7.62mm_Horizontal; MPN MF0204FTE52-1K
R9: 4.7k; R_Axial_DIN0204_L3.6mm_D1.6mm_P7.62mm_Horizontal; MPN MF0204FTE52-4K7
R13: 330; R_Axial_DIN0204_L3.6mm_D1.6mm_P7.62mm_Horizontal; MPN MF0204FTE52-330R
R26: 470k; R_Axial_DIN0204_L3.6mm_D1.6mm_P2.54mm_Vertical; MPN MBA02040C4703FRP00
U1: ESP32-DevKitC-32E; ESP32-DevKitC-32E_Socket; MPN SSW-119-01-T-S
U2: 74HC123; DIP-16_W7.62mm; MPN TC74HC123AP(F)
U3: 74HC573; DIP-20_W7.62mm; MPN SN74HC573AN

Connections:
/+3V3: C2.1, C6.1, C7.1, J1.5 (+3V3), J3.3 (+3V3), J6.2 (+3V3), R1.2, R9.1, R15.1, R17.1, R19.1, R23.1, R24.1, R25.1, R26.2, U1.1 (3V3), U2.16 (VCC), U3.20 (VCC)
/+5V: D1.2 (A), J1.1 (+5V), J1.2 (+5V)
/+5V_DK: C1.1, D1.1 (K), U1.19 (5V)
/BTN: J6.4 (BTN), R14.1
/BTN_IN: R14.2, U1.33 (IO0)
/DEFROST_FB: R8.2, U1.10 (IO26)
/DEFROST_REQ: R4.1, U1.9 (IO25), U3.2 (D1)
/DIR: J1.7 (DIR), U1.35 (IO15)
/DPS_RXD: J11.3 (DPS_RXD), R21.2
/DPS_RX_G: R22.2, U1.25 (IO21)
/DPS_TXD: J11.2 (DPS_TXD), R22.1, R23.2
/DPS_TX_G: R21.1, U1.22 (IO22)
/FAN1_PWM: J2.7 (FAN1_PWM), R7.1, U1.13 (IO12)
/FAN2_PWM: J2.8 (FAN2_PWM), U1.12 (IO14)
/FAN3_PWM: J2.9 (FAN3_PWM), U1.29 (IO5)
/GND: C1.2, C2.2, C6.2, C7.2, D3.1 (K), D9.2 (A), J1.3 (GND), J1.4 (GND), J2.1 (GND), J2.2 (GND), J2.6 (GND), J2.12 (GND), J3.1 (GND), J4.1 (GND), J4.4 (GND), J6.1 (GND), J6.5 (GND), J11.1 (GND), R2.2, R3.2, R4.2, R7.2, U1.14 (GND), U1.20 (GND), U1.26 (GND), U2.1 (1~A), U2.8 (GND), U2.9 (2~A), U3.1 (~OE), U3.3 (D2), U3.4 (D3), U3.5 (D4), U3.6 (D5), U3.7 (D6), U3.8 (D7), U3.9 (D8), U3.10 (GND)
/HOME: J3.2 (HOME), R15.2, R16.1
/HOME_IN: R16.2, U1.21 (IO23)
/K1_ON: J2.3 (K1_ON), U2.13 (1Q)
/K2_ON: J2.4 (K2_ON), R8.1, U3.19 (Q1)
/LATCH_DLY: R5.1, U2.12 (2~Q)
/LATCH_EN: D2.2 (A), R5.2, U3.11 (LE)
/LATCH_RAW: D2.1 (K), U2.4 (1~Q), U2.10 (2B), U2.11 (2~CLR)
/LD_C: C5.1, U2.6 (2Cext)
/LD_RC: C5.2, R26.1, U2.7 (2Rext/Cext)
/LEAK: J4.3 (LEAK), R19.2, R20.1
/LEAK_IN: R20.2, U1.4 (IO39)
/LED_EXT: D3.2 (A), J6.3 (LED_EXT), R13.2
/LED_G: R13.1, U1.34 (IO2)
/LID: J4.2 (LID), R17.2, R18.1
/LID_IN: R18.2, U1.11 (IO27)
/MOT_EN: J1.8 (MOT_EN), U1.27 (IO19)
/OWA: J1.10 (OWA), R9.2, U1.32 (IO4)
/OWB: J1.11 (OWB), U1.15 (IO13)
/STEP: J1.6 (STEP), U1.28 (IO18)
/TACH1: J2.10 (TACH1), R10.1, R24.2
/TACH1_IN: R10.2, U1.5 (IO34)
/TACH2: J2.11 (TACH2), R11.1, R25.2
/TACH2_IN: R11.2, U1.6 (IO35)
/TEC_EN: R2.1, U1.7 (IO32), U2.3 (1~CLR)
/THERMO_OK: J2.5 (THERMO_OK), R12.1
/THERMO_OK_IN: D9.1 (K), R12.2, U1.3 (IO36)
/TMC_TX_G: R6.1, U1.30 (IO17)
/TMC_UART: J1.9 (TMC_UART), R6.2, U1.31 (IO16)
/WDT_KICK: R3.1, U1.8 (IO33), U2.2 (1B)
/WD_C: C4.1, U2.14 (1Cext)
/WD_RC: C4.2, R1.1, U2.15 (1Rext/Cext)

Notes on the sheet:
ESP32-DevKitC-32E (socketed) and supply
Keyed links: XH-11 to pwr card, XH-12 to tec card (5 V, 3.3 V, GND and logic only)
TEC watchdog (74HC123) and defrost interlock latch (74HC573)
Lid, leak, home, UI and DPS5005 UART (3.3 V, series-protected)
